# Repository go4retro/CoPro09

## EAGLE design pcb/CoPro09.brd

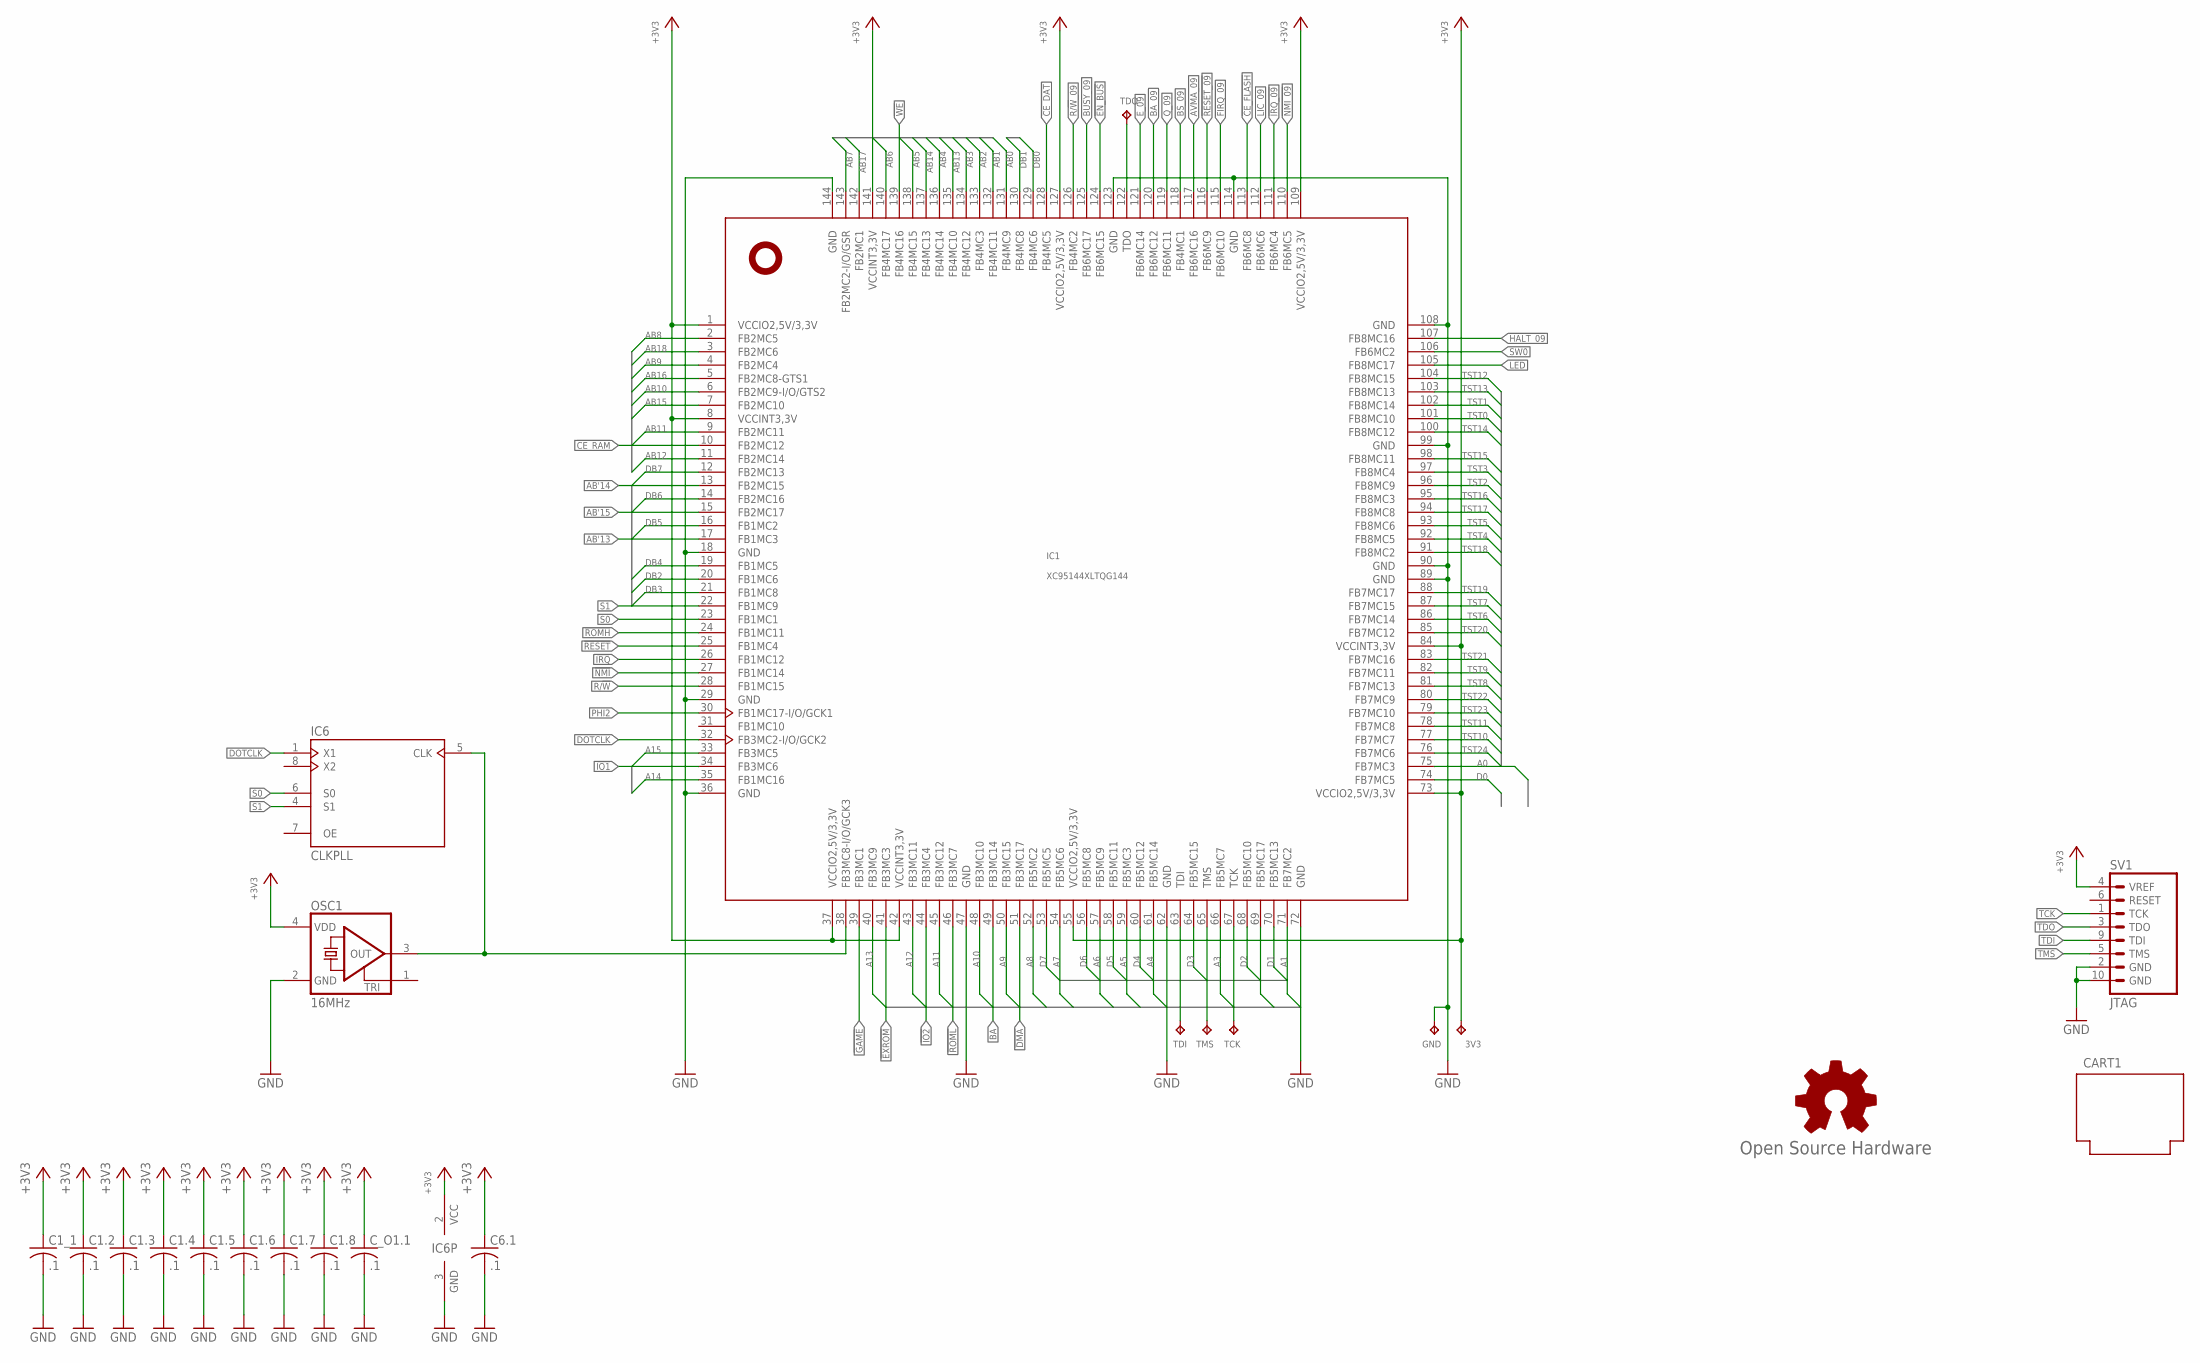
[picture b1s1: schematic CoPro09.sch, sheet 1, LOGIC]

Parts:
3V3: TPTP08R; TP08R
C1.2, C1.3, C1.4, C1.5, C1.6, C1.7, C1.8, C1_1, C6.1: .1; C0402
CART1: CARTRIDGE_C64
C_O1.1: .1; C0402
GND: TPTP08R; TP08R
GOLD_ORB_SM1: Open Source Hardware; OSHW_8MM
IC1: XC95144XLTQG144; TQFP144
IC6: CLKPLL; SOIC8
OSC1: 16MHz; ASE
SV1: JTAG
TCK: TPTP08R; TP08R
TDI: TPTP08R; TP08R
TDO: TPTP08R; TP08R
TMS: TPTP08R; TP08R

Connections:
!CE_DAT: IC1.128 (FB4MC5); also elsewhere on the board
!CE_FLASH: IC1.113 (FB6MC8); also elsewhere on the board
!CE_RAM: IC1.10 (FB2MC12); also elsewhere on the board
!DMA: IC1.51 (FB3MC17); also elsewhere on the board
!EN_BUS: IC1.124 (FB6MC15); also elsewhere on the board
!EXROM: IC1.41 (FB3MC3); also elsewhere on the board
!FIRQ_09: IC1.115 (FB6MC10); also elsewhere on the board
!GAME: IC1.39 (FB3MC1); also elsewhere on the board
!HALT_09: IC1.107 (FB8MC16); also elsewhere on the board
!IO1: IC1.34 (FB3MC6); also elsewhere on the board
!IO2: IC1.44 (FB3MC4); also elsewhere on the board
!IRQ: IC1.26 (FB1MC12); also elsewhere on the board
!IRQ_09: IC1.111 (FB6MC4); also elsewhere on the board
!NMI: IC1.27 (FB1MC14); also elsewhere on the board
!NMI_09: IC1.110 (FB6MC5); also elsewhere on the board
!RESET: IC1.25 (FB1MC4); also elsewhere on the board
!RESET_09: IC1.116 (FB6MC9); also elsewhere on the board
!ROMH: IC1.24 (FB1MC11); also elsewhere on the board
!ROML: IC1.46 (FB3MC7); also elsewhere on the board
!WE: IC1.139 (FB4MC16); also elsewhere on the board
+3V3: 3V3.TP, C1.2.1, C1.3.1, C1.4.1, C1.5.1, C1.6.1, C1.7.1, C1.8.1, C1_1.1, C6.1.1, C_O1.1.1, IC1.1 (VCCIO2,5V/3,3V), IC1.8 (VCCINT3,3V), IC1.37 (VCCIO2,5V/3,3V), IC1.42 (VCCINT3,3V), IC1.55 (VCCIO2,5V/3,3V), IC1.73 (VCCIO2,5V/3,3V), IC1.84 (VCCINT3,3V), IC1.109 (VCCIO2,5V/3,3V), IC1.127 (VCCIO2,5V/3,3V), IC1.141 (VCCINT3,3V), IC6.2 (VCC), OSC1.4 (VDD), SV1.4 (VREF); also elsewhere on the board
A0: IC1.75 (FB7MC3); also elsewhere on the board
A1: IC1.71 (FB7MC2); also elsewhere on the board
A2: IC1.69 (FB5MC17); also elsewhere on the board
A3: IC1.66 (FB5MC7); also elsewhere on the board
A4: IC1.61 (FB5MC14); also elsewhere on the board
A5: IC1.59 (FB5MC3); also elsewhere on the board
A6: IC1.57 (FB5MC9); also elsewhere on the board
A7: IC1.54 (FB5MC6); also elsewhere on the board
A8: IC1.52 (FB5MC2); also elsewhere on the board
A9: IC1.50 (FB3MC15); also elsewhere on the board
A10: IC1.48 (FB3MC10); also elsewhere on the board
A11: IC1.45 (FB3MC12); also elsewhere on the board
A12: IC1.43 (FB3MC11); also elsewhere on the board
A13: IC1.40 (FB3MC9); also elsewhere on the board
A14: IC1.35 (FB1MC16); also elsewhere on the board
A15: IC1.33 (FB3MC5); also elsewhere on the board
AB0: IC1.131 (FB4MC9); also elsewhere on the board
AB1: IC1.132 (FB4MC11); also elsewhere on the board
AB2: IC1.133 (FB4MC3); also elsewhere on the board
AB3: IC1.134 (FB4MC12); also elsewhere on the board
AB4: IC1.136 (FB4MC14); also elsewhere on the board
AB5: IC1.138 (FB4MC15); also elsewhere on the board
AB6: IC1.140 (FB4MC17); also elsewhere on the board
AB7: IC1.143 (FB2MC2-I/O/GSR); also elsewhere on the board
AB8: IC1.2 (FB2MC5); also elsewhere on the board
AB9: IC1.4 (FB2MC4); also elsewhere on the board
AB10: IC1.6 (FB2MC9-I/O/GTS2); also elsewhere on the board
AB11: IC1.9 (FB2MC11); also elsewhere on the board
AB12: IC1.11 (FB2MC14); also elsewhere on the board
AB13: IC1.135 (FB4MC10); also elsewhere on the board
AB14: IC1.137 (FB4MC13); also elsewhere on the board
AB15: IC1.7 (FB2MC10); also elsewhere on the board
AB16: IC1.5 (FB2MC8-GTS1); also elsewhere on the board
AB17: IC1.142 (FB2MC1); also elsewhere on the board
AB18: IC1.3 (FB2MC6); also elsewhere on the board
AB'13: IC1.17 (FB1MC3); also elsewhere on the board
AB'14: IC1.13 (FB2MC15); also elsewhere on the board
AB'15: IC1.15 (FB2MC17); also elsewhere on the board
AVMA_09: IC1.117 (FB6MC16); also elsewhere on the board
BA: IC1.49 (FB3MC14); also elsewhere on the board
BA_09: IC1.120 (FB6MC12); also elsewhere on the board
BS_09: IC1.118 (FB4MC1); also elsewhere on the board
BUSY_09: IC1.125 (FB6MC17); also elsewhere on the board
D0: IC1.74 (FB7MC5); also elsewhere on the board
D1: IC1.70 (FB5MC13); also elsewhere on the board
D2: IC1.68 (FB5MC10); also elsewhere on the board
D3: IC1.64 (FB5MC15); also elsewhere on the board
D4: IC1.60 (FB5MC12); also elsewhere on the board
D5: IC1.58 (FB5MC11); also elsewhere on the board
D6: IC1.56 (FB5MC8); also elsewhere on the board
D7: IC1.53 (FB5MC5); also elsewhere on the board
DB0: IC1.129 (FB4MC6); also elsewhere on the board
DB1: IC1.130 (FB4MC8); also elsewhere on the board
DB2: IC1.20 (FB1MC6); also elsewhere on the board
DB3: IC1.21 (FB1MC8); also elsewhere on the board
DB4: IC1.19 (FB1MC5); also elsewhere on the board
DB5: IC1.16 (FB1MC2); also elsewhere on the board
DB6: IC1.14 (FB2MC16); also elsewhere on the board
DB7: IC1.12 (FB2MC13); also elsewhere on the board
DOTCLK: IC1.32 (FB3MC2-I/O/GCK2), IC6.1 (X1); also elsewhere on the board
E_09: IC1.121 (FB6MC14); also elsewhere on the board
GND: C1.2.2, C1.3.2, C1.4.2, C1.5.2, C1.6.2, C1.7.2, C1.8.2, C1_1.2, C6.1.2, C_O1.1.2, GND.TP, IC1.18 (GND), IC1.29 (GND), IC1.36 (GND), IC1.47 (GND), IC1.62 (GND), IC1.72 (GND), IC1.89 (GND), IC1.90 (GND), IC1.99 (GND), IC1.108 (GND), IC1.114 (GND), IC1.123 (GND), IC1.144 (GND), IC6.3 (GND), OSC1.2 (GND), SV1.2 (GND), SV1.10 (GND); also elsewhere on the board
LED: IC1.105 (FB8MC17); also elsewhere on the board
LIC_09: IC1.112 (FB6MC6); also elsewhere on the board
unnamed: IC1.38 (FB3MC8-I/O/GCK3), IC6.5 (CLK), OSC1.3 (OUT)
PHI2: IC1.30 (FB1MC17-I/O/GCK1); also elsewhere on the board
Q_09: IC1.119 (FB6MC11); also elsewhere on the board
R/!W: IC1.28 (FB1MC15); also elsewhere on the board
R/!W!_09: IC1.126 (FB4MC2); also elsewhere on the board
S0: IC1.23 (FB1MC1), IC6.6 (S0)
S1: IC1.22 (FB1MC9), IC6.4 (S1)
SW0: IC1.106 (FB6MC2); also elsewhere on the board
TCK: IC1.67 (TCK), SV1.1 (TCK), TCK.TP
TDI: IC1.63 (TDI), SV1.9 (TDI), TDI.TP
TDO: IC1.122 (TDO), SV1.3 (TDO), TDO.TP
TMS: IC1.65 (TMS), SV1.5 (TMS), TMS.TP
TST0: IC1.101 (FB8MC10); also elsewhere on the board
TST1: IC1.102 (FB8MC14); also elsewhere on the board
TST2: IC1.96 (FB8MC9); also elsewhere on the board
TST3: IC1.97 (FB8MC4); also elsewhere on the board
TST4: IC1.92 (FB8MC5); also elsewhere on the board
TST5: IC1.93 (FB8MC6); also elsewhere on the board
TST6: IC1.86 (FB7MC14); also elsewhere on the board
TST7: IC1.87 (FB7MC15); also elsewhere on the board
TST8: IC1.81 (FB7MC13); also elsewhere on the board
TST9: IC1.82 (FB7MC11); also elsewhere on the board
TST10: IC1.77 (FB7MC7); also elsewhere on the board
TST11: IC1.78 (FB7MC8); also elsewhere on the board
TST12: IC1.104 (FB8MC15); also elsewhere on the board
TST13: IC1.103 (FB8MC13); also elsewhere on the board
TST14: IC1.100 (FB8MC12); also elsewhere on the board
TST15: IC1.98 (FB8MC11); also elsewhere on the board
TST16: IC1.95 (FB8MC3); also elsewhere on the board
TST17: IC1.94 (FB8MC8); also elsewhere on the board
TST18: IC1.91 (FB8MC2); also elsewhere on the board
TST19: IC1.88 (FB7MC17); also elsewhere on the board
TST20: IC1.85 (FB7MC12); also elsewhere on the board
TST21: IC1.83 (FB7MC16); also elsewhere on the board
TST22: IC1.80 (FB7MC9); also elsewhere on the board
TST23: IC1.79 (FB7MC10); also elsewhere on the board
TST24: IC1.76 (FB7MC6); also elsewhere on the board

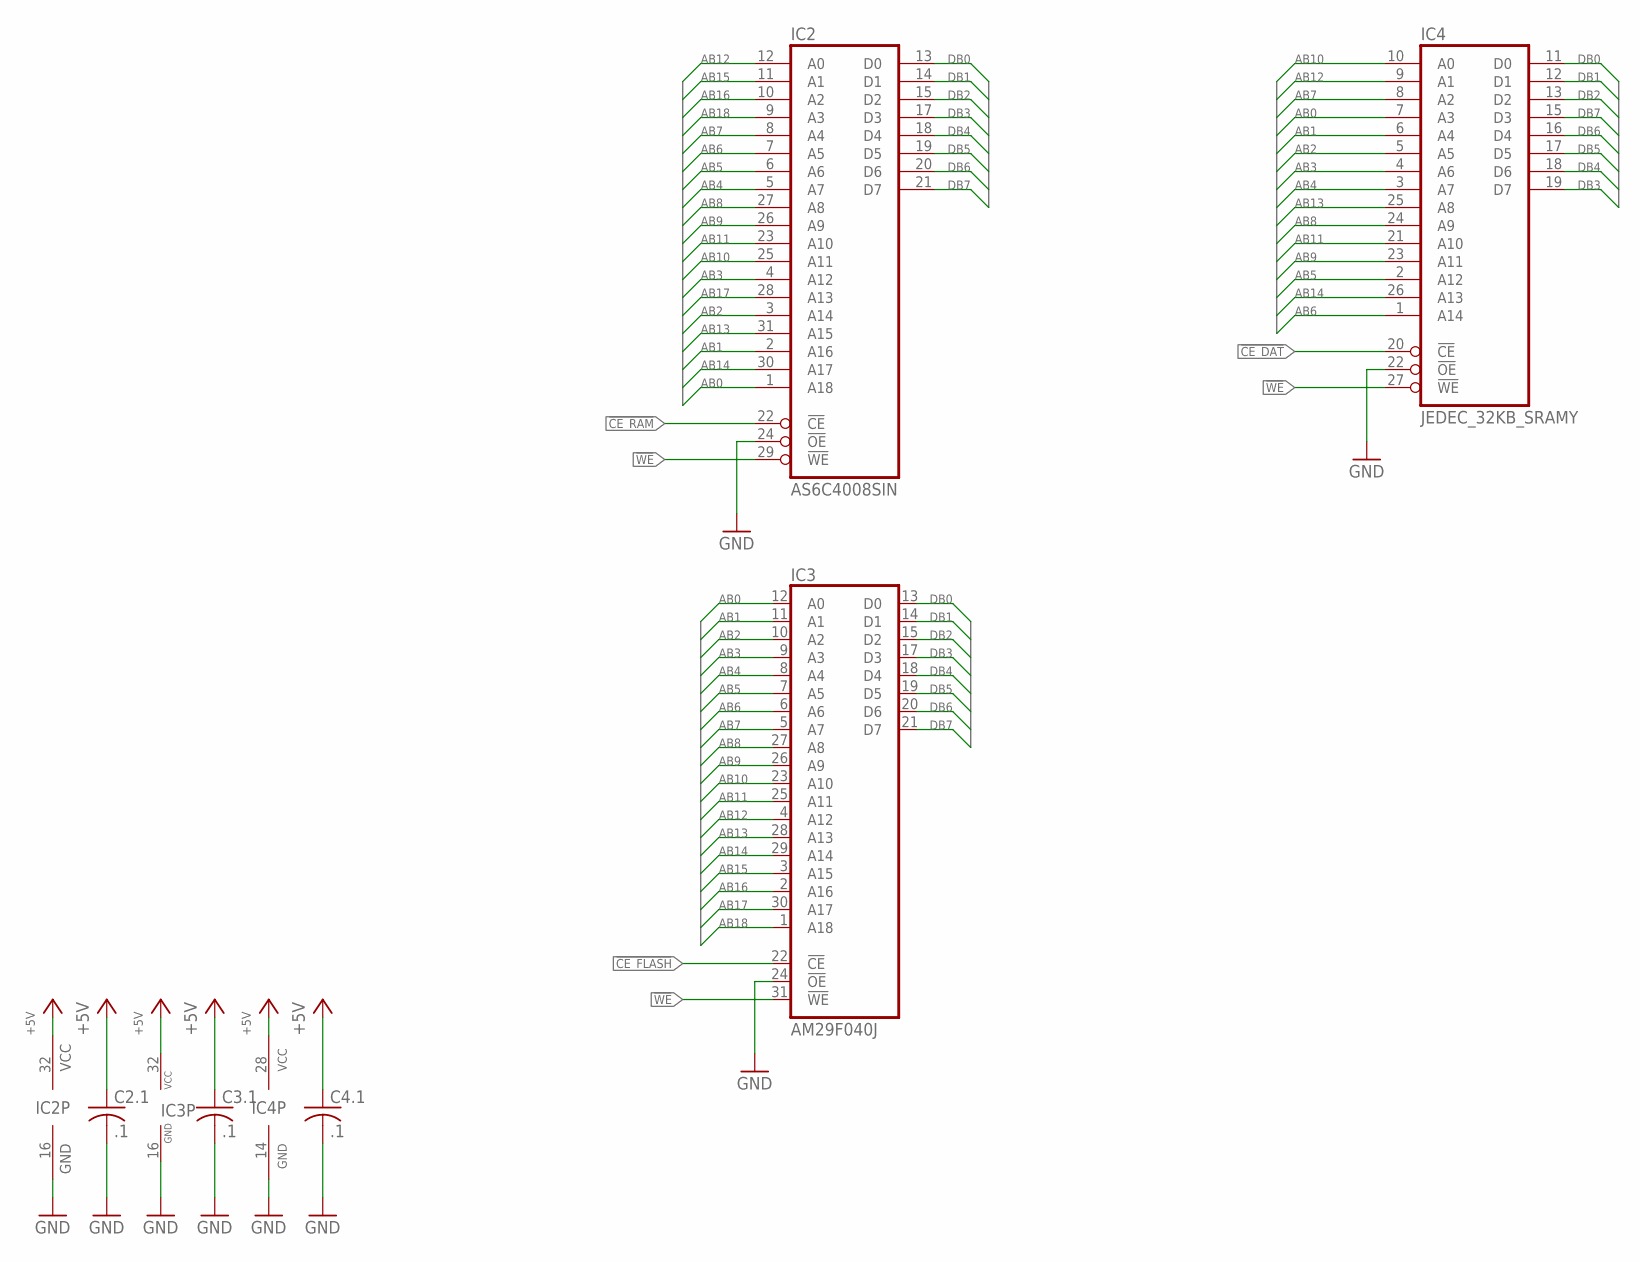
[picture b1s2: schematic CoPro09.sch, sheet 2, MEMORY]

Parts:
C2.1, C3.1, C4.1: .1; C0402
IC2: AS6C4008SIN; SOP32L
IC3: AM29F040J; PLCC32R
IC4: JEDEC_32KB_SRAMY; SOJ32/3

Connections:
!CE_DAT: IC4.20 (!CE); also elsewhere on the board
!CE_FLASH: IC3.22 (!CE); also elsewhere on the board
!CE_RAM: IC2.22 (!CE); also elsewhere on the board
!WE: IC2.29 (!WE), IC3.31 (!WE), IC4.27 (!WE); also elsewhere on the board
+5V: C2.1.1, C3.1.1, C4.1.1, IC2.32 (VCC), IC3.32 (VCC), IC4.28 (VCC); also elsewhere on the board
AB0: IC2.1 (A18), IC3.12 (A0), IC4.7 (A3); also elsewhere on the board
AB1: IC2.2 (A16), IC3.11 (A1), IC4.6 (A4); also elsewhere on the board
AB2: IC2.3 (A14), IC3.10 (A2), IC4.5 (A5); also elsewhere on the board
AB3: IC2.4 (A12), IC3.9 (A3), IC4.4 (A6); also elsewhere on the board
AB4: IC2.5 (A7), IC3.8 (A4), IC4.3 (A7); also elsewhere on the board
AB5: IC2.6 (A6), IC3.7 (A5), IC4.2 (A12); also elsewhere on the board
AB6: IC2.7 (A5), IC3.6 (A6), IC4.1 (A14); also elsewhere on the board
AB7: IC2.8 (A4), IC3.5 (A7), IC4.8 (A2); also elsewhere on the board
AB8: IC2.27 (A8), IC3.27 (A8), IC4.24 (A9); also elsewhere on the board
AB9: IC2.26 (A9), IC3.26 (A9), IC4.23 (A11); also elsewhere on the board
AB10: IC2.25 (A11), IC3.23 (A10), IC4.10 (A0); also elsewhere on the board
AB11: IC2.23 (A10), IC3.25 (A11), IC4.21 (A10); also elsewhere on the board
AB12: IC2.12 (A0), IC3.4 (A12), IC4.9 (A1); also elsewhere on the board
AB13: IC2.31 (A15), IC3.28 (A13), IC4.25 (A8); also elsewhere on the board
AB14: IC2.30 (A17), IC3.29 (A14), IC4.26 (A13); also elsewhere on the board
AB15: IC2.11 (A1), IC3.3 (A15); also elsewhere on the board
AB16: IC2.10 (A2), IC3.2 (A16); also elsewhere on the board
AB17: IC2.28 (A13), IC3.30 (A17); also elsewhere on the board
AB18: IC2.9 (A3), IC3.1 (A18); also elsewhere on the board
DB0: IC2.13 (D0), IC3.13 (D0), IC4.11 (D0); also elsewhere on the board
DB1: IC2.14 (D1), IC3.14 (D1), IC4.12 (D1); also elsewhere on the board
DB2: IC2.15 (D2), IC3.15 (D2), IC4.13 (D2); also elsewhere on the board
DB3: IC2.17 (D3), IC3.17 (D3), IC4.19 (D7); also elsewhere on the board
DB4: IC2.18 (D4), IC3.18 (D4), IC4.18 (D6); also elsewhere on the board
DB5: IC2.19 (D5), IC3.19 (D5), IC4.17 (D5); also elsewhere on the board
DB6: IC2.20 (D6), IC3.20 (D6), IC4.16 (D4); also elsewhere on the board
DB7: IC2.21 (D7), IC3.21 (D7), IC4.15 (D3); also elsewhere on the board
GND: C2.1.2, C3.1.2, C4.1.2, IC2.16 (GND), IC2.24 (!OE), IC3.16 (GND), IC3.24 (!OE), IC4.14 (GND), IC4.22 (!OE); also elsewhere on the board

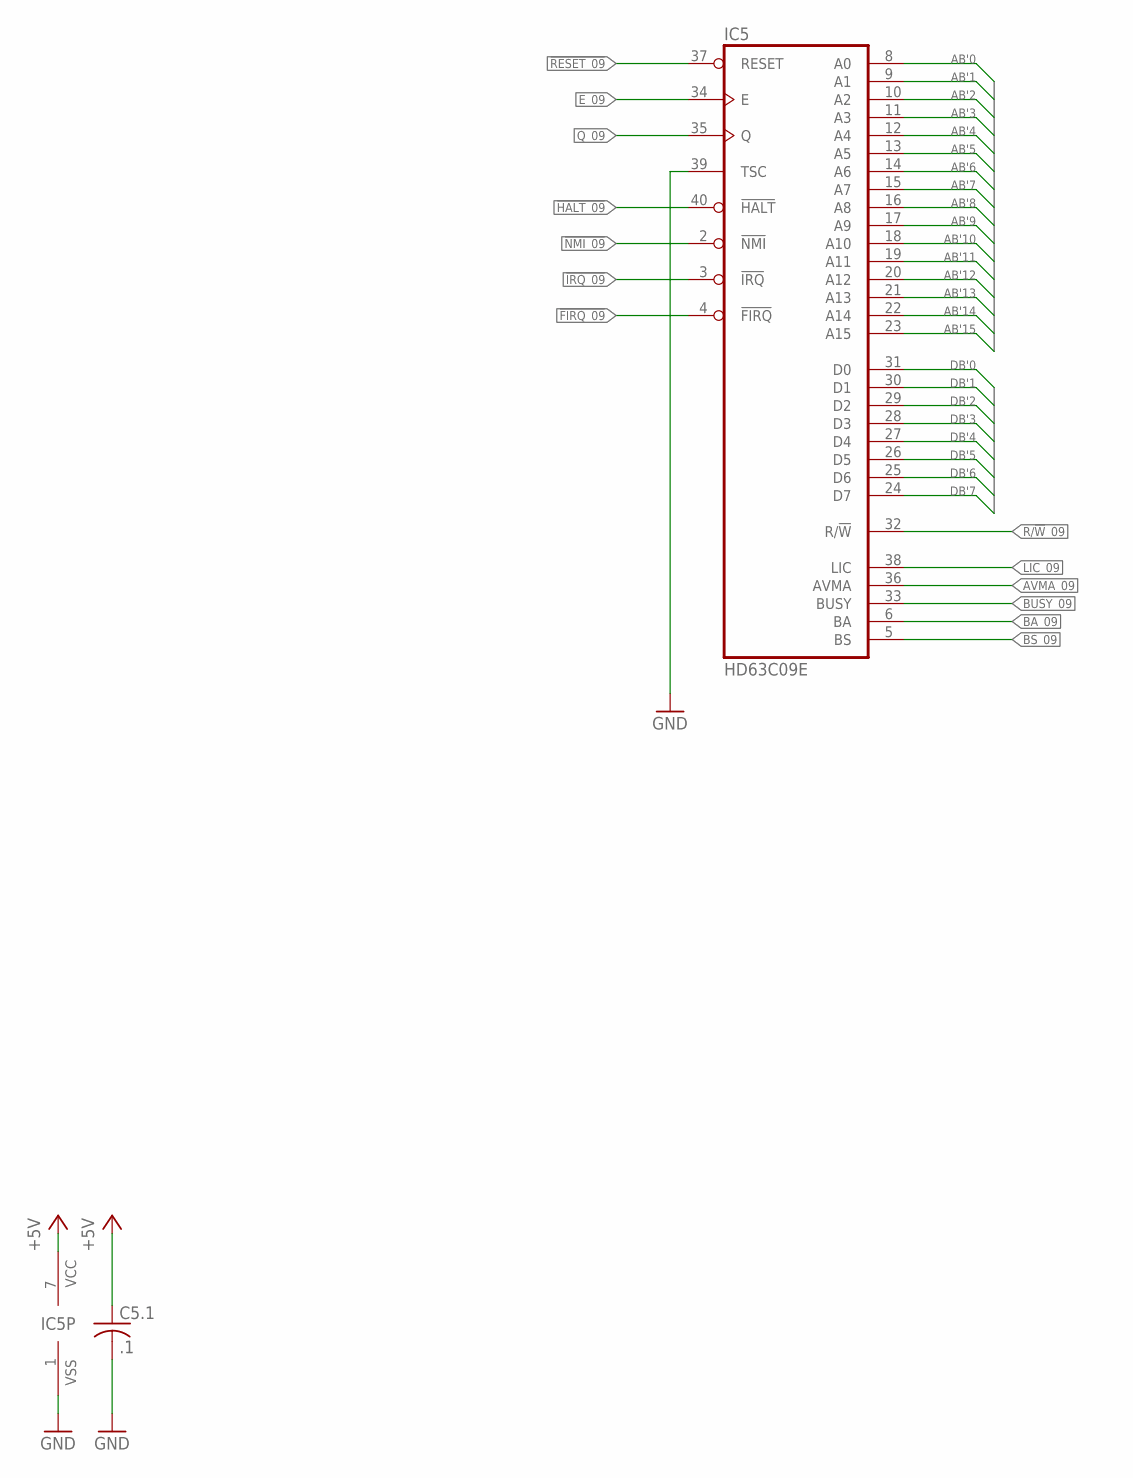
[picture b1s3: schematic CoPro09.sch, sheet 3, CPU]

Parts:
C5.1: .1; C0402
IC5: HD63C09E; DIL40-ROUNDPAD

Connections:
!FIRQ_09: IC5.4 (!FIRQ); also elsewhere on the board
!HALT_09: IC5.40 (!HALT); also elsewhere on the board
!IRQ_09: IC5.3 (!IRQ); also elsewhere on the board
!NMI_09: IC5.2 (!NMI); also elsewhere on the board
!RESET_09: IC5.37 (RESET); also elsewhere on the board
+5V: C5.1.1, IC5.7 (VCC); also elsewhere on the board
AB'0: IC5.8 (A0); also elsewhere on the board
AB'1: IC5.9 (A1); also elsewhere on the board
AB'2: IC5.10 (A2); also elsewhere on the board
AB'3: IC5.11 (A3); also elsewhere on the board
AB'4: IC5.12 (A4); also elsewhere on the board
AB'5: IC5.13 (A5); also elsewhere on the board
AB'6: IC5.14 (A6); also elsewhere on the board
AB'7: IC5.15 (A7); also elsewhere on the board
AB'8: IC5.16 (A8); also elsewhere on the board
AB'9: IC5.17 (A9); also elsewhere on the board
AB'10: IC5.18 (A10); also elsewhere on the board
AB'11: IC5.19 (A11); also elsewhere on the board
AB'12: IC5.20 (A12); also elsewhere on the board
AB'13: IC5.21 (A13); also elsewhere on the board
AB'14: IC5.22 (A14); also elsewhere on the board
AB'15: IC5.23 (A15); also elsewhere on the board
AVMA_09: IC5.36 (AVMA); also elsewhere on the board
BA_09: IC5.6 (BA); also elsewhere on the board
BS_09: IC5.5 (BS); also elsewhere on the board
BUSY_09: IC5.33 (BUSY); also elsewhere on the board
DB'0: IC5.31 (D0); also elsewhere on the board
DB'1: IC5.30 (D1); also elsewhere on the board
DB'2: IC5.29 (D2); also elsewhere on the board
DB'3: IC5.28 (D3); also elsewhere on the board
DB'4: IC5.27 (D4); also elsewhere on the board
DB'5: IC5.26 (D5); also elsewhere on the board
DB'6: IC5.25 (D6); also elsewhere on the board
DB'7: IC5.24 (D7); also elsewhere on the board
E_09: IC5.34 (E); also elsewhere on the board
GND: C5.1.2, IC5.1 (VSS), IC5.39 (TSC); also elsewhere on the board
LIC_09: IC5.38 (LIC); also elsewhere on the board
Q_09: IC5.35 (Q); also elsewhere on the board
R/!W!_09: IC5.32 (R/!W); also elsewhere on the board

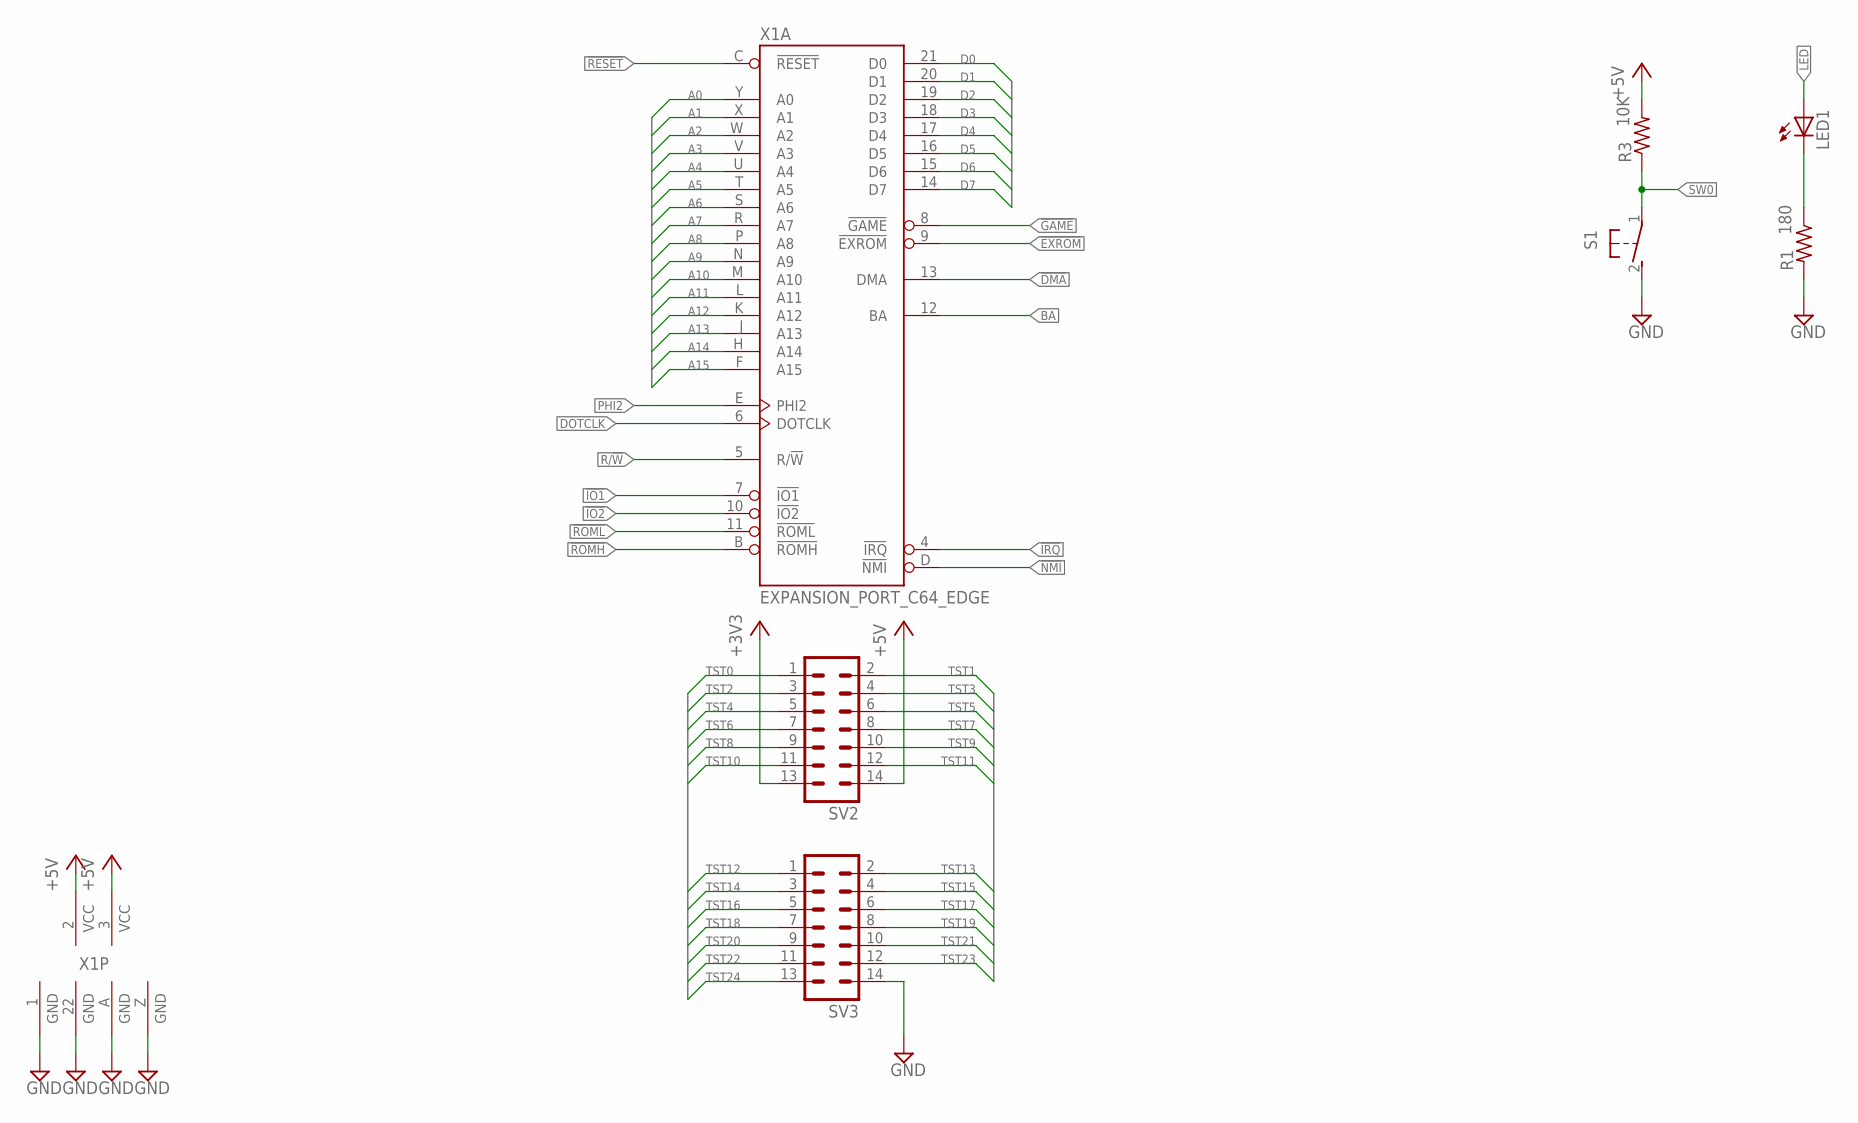
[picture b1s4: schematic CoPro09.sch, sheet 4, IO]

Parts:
LED1: LED3MM
R1: 180; R0402
R3: 10K; R0402
S1: 31-XX; B3F-31XX
SV2, SV3: MA07-2
X1: EXPANSION_PORT_C64_EDGE; MA100-22-2

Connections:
!DMA: X1.13 (DMA); also elsewhere on the board
!EXROM: X1.9 (!EXROM); also elsewhere on the board
!GAME: X1.8 (!GAME); also elsewhere on the board
!IO1: X1.7 (!IO1); also elsewhere on the board
!IO2: X1.10 (!IO2); also elsewhere on the board
!IRQ: X1.4 (!IRQ); also elsewhere on the board
!NMI: X1.D (!NMI); also elsewhere on the board
!RESET: X1.C (!RESET); also elsewhere on the board
!ROMH: X1.B (!ROMH); also elsewhere on the board
!ROML: X1.11 (!ROML); also elsewhere on the board
+3V3: SV2.13; also elsewhere on the board
+5V: R3.2, SV2.14, X1.2 (VCC), X1.3 (VCC); also elsewhere on the board
A0: X1.Y (A0); also elsewhere on the board
A1: X1.X (A1); also elsewhere on the board
A2: X1.W (A2); also elsewhere on the board
A3: X1.V (A3); also elsewhere on the board
A4: X1.U (A4); also elsewhere on the board
A5: X1.T (A5); also elsewhere on the board
A6: X1.S (A6); also elsewhere on the board
A7: X1.R (A7); also elsewhere on the board
A8: X1.P (A8); also elsewhere on the board
A9: X1.N (A9); also elsewhere on the board
A10: X1.M (A10); also elsewhere on the board
A11: X1.L (A11); also elsewhere on the board
A12: X1.K (A12); also elsewhere on the board
A13: X1.J (A13); also elsewhere on the board
A14: X1.H (A14); also elsewhere on the board
A15: X1.F (A15); also elsewhere on the board
BA: X1.12 (BA); also elsewhere on the board
D0: X1.21 (D0); also elsewhere on the board
D1: X1.20 (D1); also elsewhere on the board
D2: X1.19 (D2); also elsewhere on the board
D3: X1.18 (D3); also elsewhere on the board
D4: X1.17 (D4); also elsewhere on the board
D5: X1.16 (D5); also elsewhere on the board
D6: X1.15 (D6); also elsewhere on the board
D7: X1.14 (D7); also elsewhere on the board
DOTCLK: X1.6 (DOTCLK); also elsewhere on the board
GND: R1.2, S1.2 (S), SV3.14, X1.1 (GND), X1.22 (GND), X1.A (GND), X1.Z (GND); also elsewhere on the board
LED: LED1.A; also elsewhere on the board
unnamed: LED1.K (C), R1.1
PHI2: X1.E (PHI2); also elsewhere on the board
R/!W: X1.5 (R/!W); also elsewhere on the board
SW0: R3.1, S1.1; also elsewhere on the board
TST0: SV2.1; also elsewhere on the board
TST1: SV2.2; also elsewhere on the board
TST2: SV2.3; also elsewhere on the board
TST3: SV2.4; also elsewhere on the board
TST4: SV2.5; also elsewhere on the board
TST5: SV2.6; also elsewhere on the board
TST6: SV2.7; also elsewhere on the board
TST7: SV2.8; also elsewhere on the board
TST8: SV2.9; also elsewhere on the board
TST9: SV2.10; also elsewhere on the board
TST10: SV2.11; also elsewhere on the board
TST11: SV2.12; also elsewhere on the board
TST12: SV3.1; also elsewhere on the board
TST13: SV3.2; also elsewhere on the board
TST14: SV3.3; also elsewhere on the board
TST15: SV3.4; also elsewhere on the board
TST16: SV3.5; also elsewhere on the board
TST17: SV3.6; also elsewhere on the board
TST18: SV3.7; also elsewhere on the board
TST19: SV3.8; also elsewhere on the board
TST20: SV3.9; also elsewhere on the board
TST21: SV3.10; also elsewhere on the board
TST22: SV3.11; also elsewhere on the board
TST23: SV3.12; also elsewhere on the board
TST24: SV3.13; also elsewhere on the board

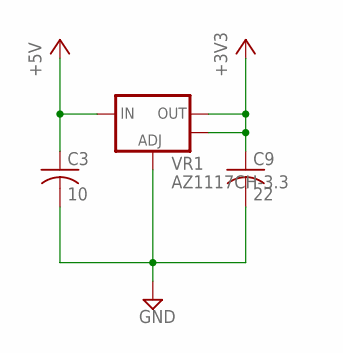
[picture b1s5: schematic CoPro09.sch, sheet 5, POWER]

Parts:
C3: 10; C0805
C9: 22; C0805
VR1: AZ1117CH-3.3; SOT223

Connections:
+3V3: C9.1, VR1.2 (OUT), VR1.4 (OUT); also elsewhere on the board
+5V: C3.1, VR1.3 (IN); also elsewhere on the board
GND: C3.2, C9.2, VR1.1 (ADJ); also elsewhere on the board

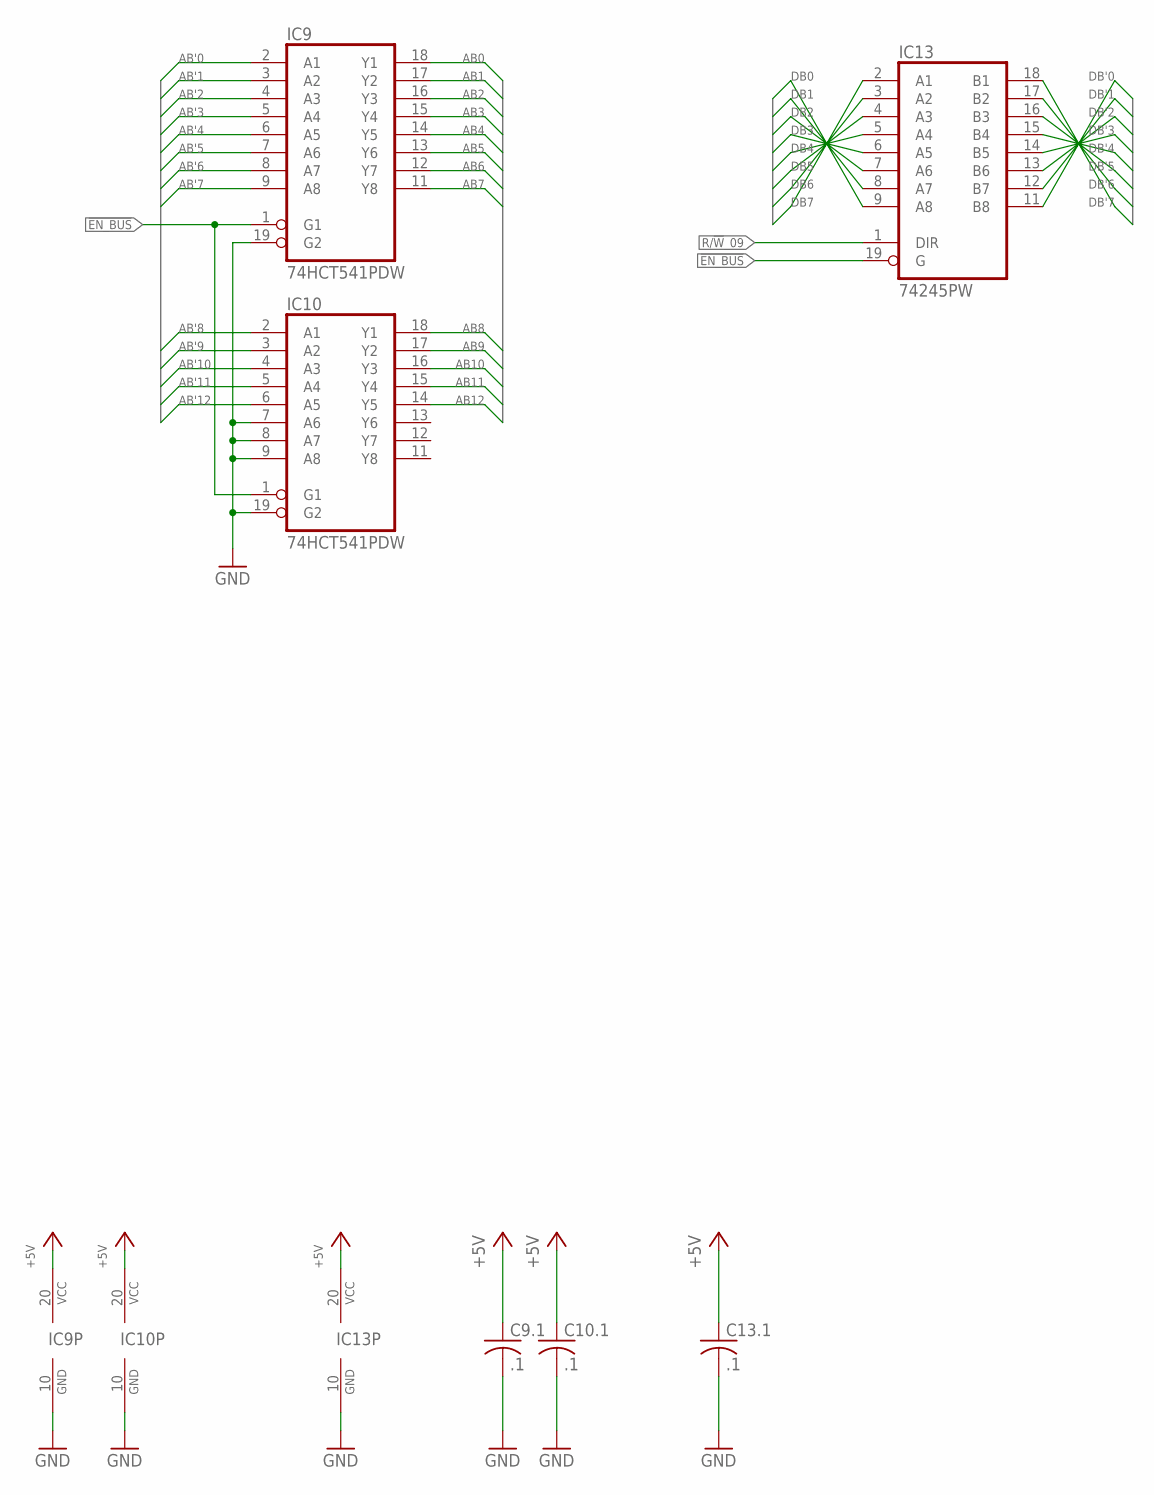
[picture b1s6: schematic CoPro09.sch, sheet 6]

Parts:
C9.1, C10.1, C13.1: .1; C0402
IC9, IC10: 74HCT541PDW; TSSOP20
IC13: 74245PW; TSSOP20

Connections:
!EN_BUS: IC9.1 (G1), IC10.1 (G1), IC13.19 (G); also elsewhere on the board
+5V: C9.1.1, C10.1.1, C13.1.1, IC9.20 (VCC), IC10.20 (VCC), IC13.20 (VCC); also elsewhere on the board
AB0: IC9.18 (Y1); also elsewhere on the board
AB1: IC9.17 (Y2); also elsewhere on the board
AB2: IC9.16 (Y3); also elsewhere on the board
AB3: IC9.15 (Y4); also elsewhere on the board
AB4: IC9.14 (Y5); also elsewhere on the board
AB5: IC9.13 (Y6); also elsewhere on the board
AB6: IC9.12 (Y7); also elsewhere on the board
AB7: IC9.11 (Y8); also elsewhere on the board
AB8: IC10.18 (Y1); also elsewhere on the board
AB9: IC10.17 (Y2); also elsewhere on the board
AB10: IC10.16 (Y3); also elsewhere on the board
AB11: IC10.15 (Y4); also elsewhere on the board
AB12: IC10.14 (Y5); also elsewhere on the board
AB'0: IC9.2 (A1); also elsewhere on the board
AB'1: IC9.3 (A2); also elsewhere on the board
AB'2: IC9.4 (A3); also elsewhere on the board
AB'3: IC9.5 (A4); also elsewhere on the board
AB'4: IC9.6 (A5); also elsewhere on the board
AB'5: IC9.7 (A6); also elsewhere on the board
AB'6: IC9.8 (A7); also elsewhere on the board
AB'7: IC9.9 (A8); also elsewhere on the board
AB'8: IC10.2 (A1); also elsewhere on the board
AB'9: IC10.3 (A2); also elsewhere on the board
AB'10: IC10.4 (A3); also elsewhere on the board
AB'11: IC10.5 (A4); also elsewhere on the board
AB'12: IC10.6 (A5); also elsewhere on the board
DB0: IC13.9 (A8); also elsewhere on the board
DB1: IC13.8 (A7); also elsewhere on the board
DB2: IC13.7 (A6); also elsewhere on the board
DB3: IC13.6 (A5); also elsewhere on the board
DB4: IC13.5 (A4); also elsewhere on the board
DB5: IC13.4 (A3); also elsewhere on the board
DB6: IC13.3 (A2); also elsewhere on the board
DB7: IC13.2 (A1); also elsewhere on the board
DB'0: IC13.11 (B8); also elsewhere on the board
DB'1: IC13.12 (B7); also elsewhere on the board
DB'2: IC13.13 (B6); also elsewhere on the board
DB'3: IC13.14 (B5); also elsewhere on the board
DB'4: IC13.15 (B4); also elsewhere on the board
DB'5: IC13.16 (B3); also elsewhere on the board
DB'6: IC13.17 (B2); also elsewhere on the board
DB'7: IC13.18 (B1); also elsewhere on the board
GND: C9.1.2, C10.1.2, C13.1.2, IC9.10 (GND), IC9.19 (G2), IC10.7 (A6), IC10.8 (A7), IC10.9 (A8), IC10.10 (GND), IC10.19 (G2), IC13.10 (GND); also elsewhere on the board
R/!W!_09: IC13.1 (DIR); also elsewhere on the board

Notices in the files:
parts and their libraries:
SparkFun: Licensing: CC v3.0 Share-Alike You are welcome to use this library for commercial purposes.
